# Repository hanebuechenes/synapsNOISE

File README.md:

# synapsNOISE

**synapsNOISE** ist ein analoges Eurorack-Rauschmodul, das eine Vielzahl unterschiedlicher Rauschfarben sowie eine ansteuerbare „Grainy“-Shaper-Sektion bereitstellt. Das Modul wurde entwickelt, um von klassischem weißem Rauschen bis hin zu rauen, texturierten und CV-modulierbaren Rauschstrukturen alles zu liefern.

---

## Funktionen & Signalwege

* **Rauschfarben**: Bereitstellung verschiedener gefilterter Rauschspektren (Weiß, Rot, Pink, Blau, Violett).
* **Grainy-Sektion**: Spezieller Shaper-Zweig mit Dioden-Clipping und CV-Modulation zur Erzeugung von körnigen, raueren Rauschtexturen.
* **Mixer-Stufe**: Integrierter 6-Kanal-Summierer (basierend auf TL072) zum stufenlosen Mischen und Anpassen der Pegel an einem gemeinsamen Ausgang (`Mix Out`).
* **Eingangs- / Generator-Stufen**: Kombiniert Zener-Rauschen, Transistor-Rauschen und logikbasierte Rauschstrukturen (CD4093).

---

## Hardware-Struktur

Das Projekt ist modular im KiCad-Schaltplan aufgeteilt:
* `synapsNOISE.kicad_sch` (Hauptschaltplan)
* `noisesources.kicad_sch` (Rauschquellen)
* `rednoise.kicad_sch`, `pinknoise.kicad_sch`, `bluenoise.kicad_sch`, `violetnoise.kicad_sch` (Filterstufen)
* `grainyout.kicad_sch` (Grainy-Shaper & CV-Sektion)
* `mixer.kicad_sch` (Summierer und Ausgangsstufe)
* `power.kicad_sch` (Stromversorgung & Filterung)

---

## Produktion & Fertigung

Im Ordner `production/` befinden sich alle relevanten Daten für die Leiterplattenfertigung und Bestückung:
* Gerber- und Bohrdateien (`synapsNOISE.zip`)
* Stückliste (`bom.csv` / `bom.ods`)
* Bestückungspositionen (`positions.csv`)

---

## Lizenz & Rechtliches

Dieses Projekt ist Open-Source-Hardware und Open-Source-Software. Die jeweiligen Komponenten unterliegen den folgenden Lizenzen:

| Komponente | Lizenz | Beschreibung |
| :--- | :--- | :--- |
| **Hardware & Platinen** | [CERN OHL v2.0](https://ohwr.org/cernohl) | Gilt für Schaltpläne, PCB-Layouts und CAD-Dateien. |
| **Firmware & Code** | [MIT License](https://opensource.org/licenses/MIT) | Gilt für jeglichen Software- oder Skriptcode im Repository. |

*Entwickelt als Teil der Open-Source Eurorack-Initiative `synaps`. Bei Nachbau, Modifikation oder kommerzieller Nutzung sind die jeweiligen Lizenzbedingungen zu beachten.*

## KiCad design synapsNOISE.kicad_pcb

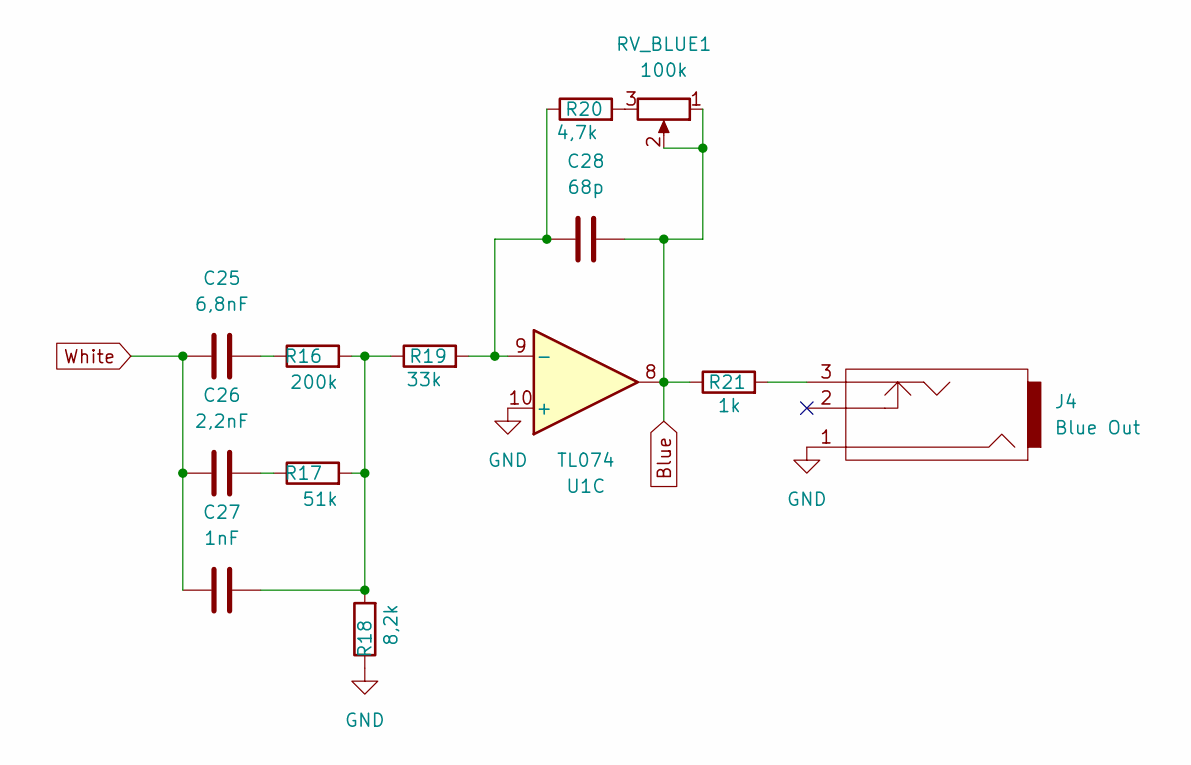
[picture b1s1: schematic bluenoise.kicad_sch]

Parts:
C25: 6,8nF; C_0603_1608Metric_Pad1.08x0.95mm_HandSolder
C26: 2,2nF; C_0603_1608Metric_Pad1.08x0.95mm_HandSolder
C27: 1nF; C_0603_1608Metric_Pad1.08x0.95mm_HandSolder
C28: 68p; C_0603_1608Metric_Pad1.08x0.95mm_HandSolder
J4: Blue Out; PJ301M-12; MFG Part Number WQP-WQP518MA; Digikey Part Number N/A
R16: 200k; R_0603_1608Metric_Pad0.98x0.95mm_HandSolder
R17: 51k; R_0603_1608Metric_Pad0.98x0.95mm_HandSolder
R18: 8,2k; R_0603_1608Metric_Pad0.98x0.95mm_HandSolder
R19: 33k; R_0603_1608Metric_Pad0.98x0.95mm_HandSolder
R20: 4,7k; R_0603_1608Metric_Pad0.98x0.95mm_HandSolder
R21: 1k; R_0603_1608Metric_Pad0.98x0.95mm_HandSolder
RV_BLUE1: 100k; RES-TH_RK09K1130A70
U1: TL074; SOIC-14_3.9x8.7mm_P1.27mm

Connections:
GND: J4.1, R18.1, U1.10 (+); also elsewhere on the board
unnamed: C25.1, R16.1
unnamed: C26.1, R17.1
unnamed: C27.1, R16.2, R17.2, R18.2, R19.1
unnamed: C28.1, R21.1, RV_BLUE1.1, RV_BLUE1.2, U1.8
unnamed: J4.3, R21.2
unnamed: R20.2, RV_BLUE1.3
unnamed: C28.2, R19.2, R20.1, U1.9 (-)
White: C25.2, C26.2, C27.2; also elsewhere on the board

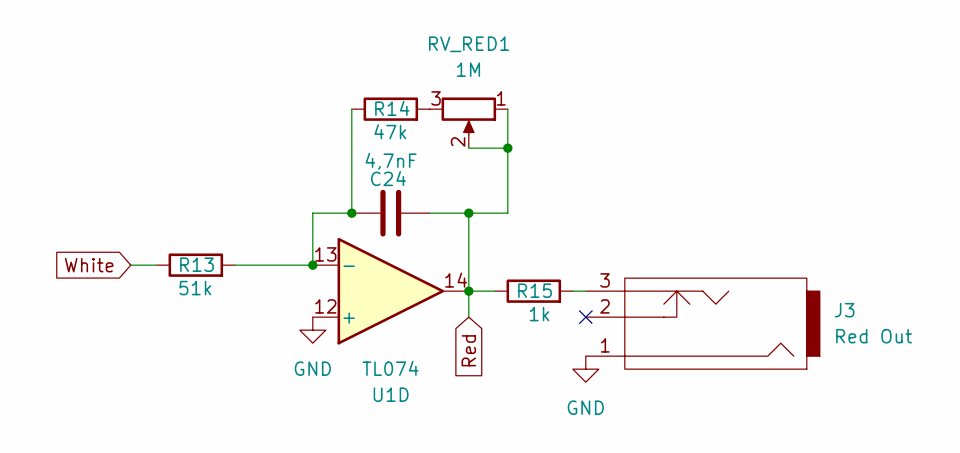
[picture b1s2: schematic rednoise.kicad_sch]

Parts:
C24: 4,7nF; C_0603_1608Metric_Pad1.08x0.95mm_HandSolder
J3: Red Out; PJ301M-12; MFG Part Number WQP-WQP518MA; Digikey Part Number N/A
R13: 51k; R_0603_1608Metric_Pad0.98x0.95mm_HandSolder
R14: 47k; R_0603_1608Metric_Pad0.98x0.95mm_HandSolder
R15: 1k; R_0603_1608Metric_Pad0.98x0.95mm_HandSolder
RV_RED1: 1M; RES-TH_RK09K1130A70
U1: TL074; SOIC-14_3.9x8.7mm_P1.27mm

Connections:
GND: J3.1, U1.12 (+); also elsewhere on the board
unnamed: C24.1, R15.1, RV_RED1.1, RV_RED1.2, U1.14
unnamed: J3.3, R15.2
unnamed: R14.2, RV_RED1.3
unnamed: C24.2, R13.2, R14.1, U1.13 (-)
White: R13.1; also elsewhere on the board

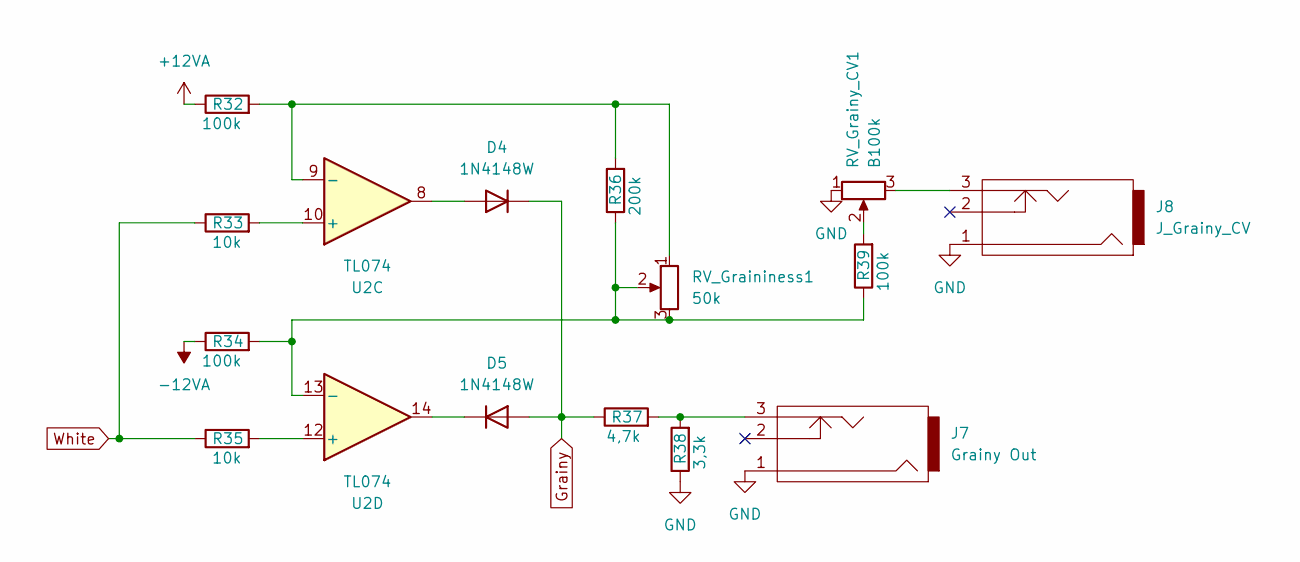
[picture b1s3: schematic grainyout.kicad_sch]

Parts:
D4, D5: 1N4148W; D_SOD-123
J7: Grainy Out; PJ301M-12; MFG Part Number WQP-WQP518MA; Digikey Part Number N/A
J8: J_Grainy_CV; PJ301M-12; MFG Part Number WQP-WQP518MA; Digikey Part Number N/A
R32, R34, R39: 100k; R_0603_1608Metric_Pad0.98x0.95mm_HandSolder
R33, R35: 10k; R_0603_1608Metric_Pad0.98x0.95mm_HandSolder
R36: 200k; R_0603_1608Metric_Pad0.98x0.95mm_HandSolder
R37: 4,7k; R_0603_1608Metric_Pad0.98x0.95mm_HandSolder
R38: 3,3k; R_0603_1608Metric_Pad0.98x0.95mm_HandSolder
RV_Graininess1: 50k; RES-TH_RK09K1130A70
RV_Grainy_CV1: B100k; RES-TH_RK09K1130A70
U2: TL074; SOIC-14_3.9x8.7mm_P1.27mm

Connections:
+12VA: R32.1; also elsewhere on the board
-12VA: R34.1; also elsewhere on the board
GND: J7.1, J8.1, R38.1, RV_Grainy_CV1.1; also elsewhere on the board
unnamed: D4.2 (A), U2.8
unnamed: D4.1 (K), D5.2 (A), R37.1
unnamed: D5.1 (K), U2.14
unnamed: J7.3, R37.2, R38.2
unnamed: J8.3, RV_Grainy_CV1.3
unnamed: R39.2, RV_Grainy_CV1.2
unnamed: R33.2, U2.10 (+)
unnamed: R32.2, R36.2, RV_Graininess1.1, U2.9 (-)
unnamed: R35.2, U2.12 (+)
unnamed: R34.2, R36.1, R39.1, RV_Graininess1.2, RV_Graininess1.3, U2.13 (-)
White: R33.1, R35.1; also elsewhere on the board

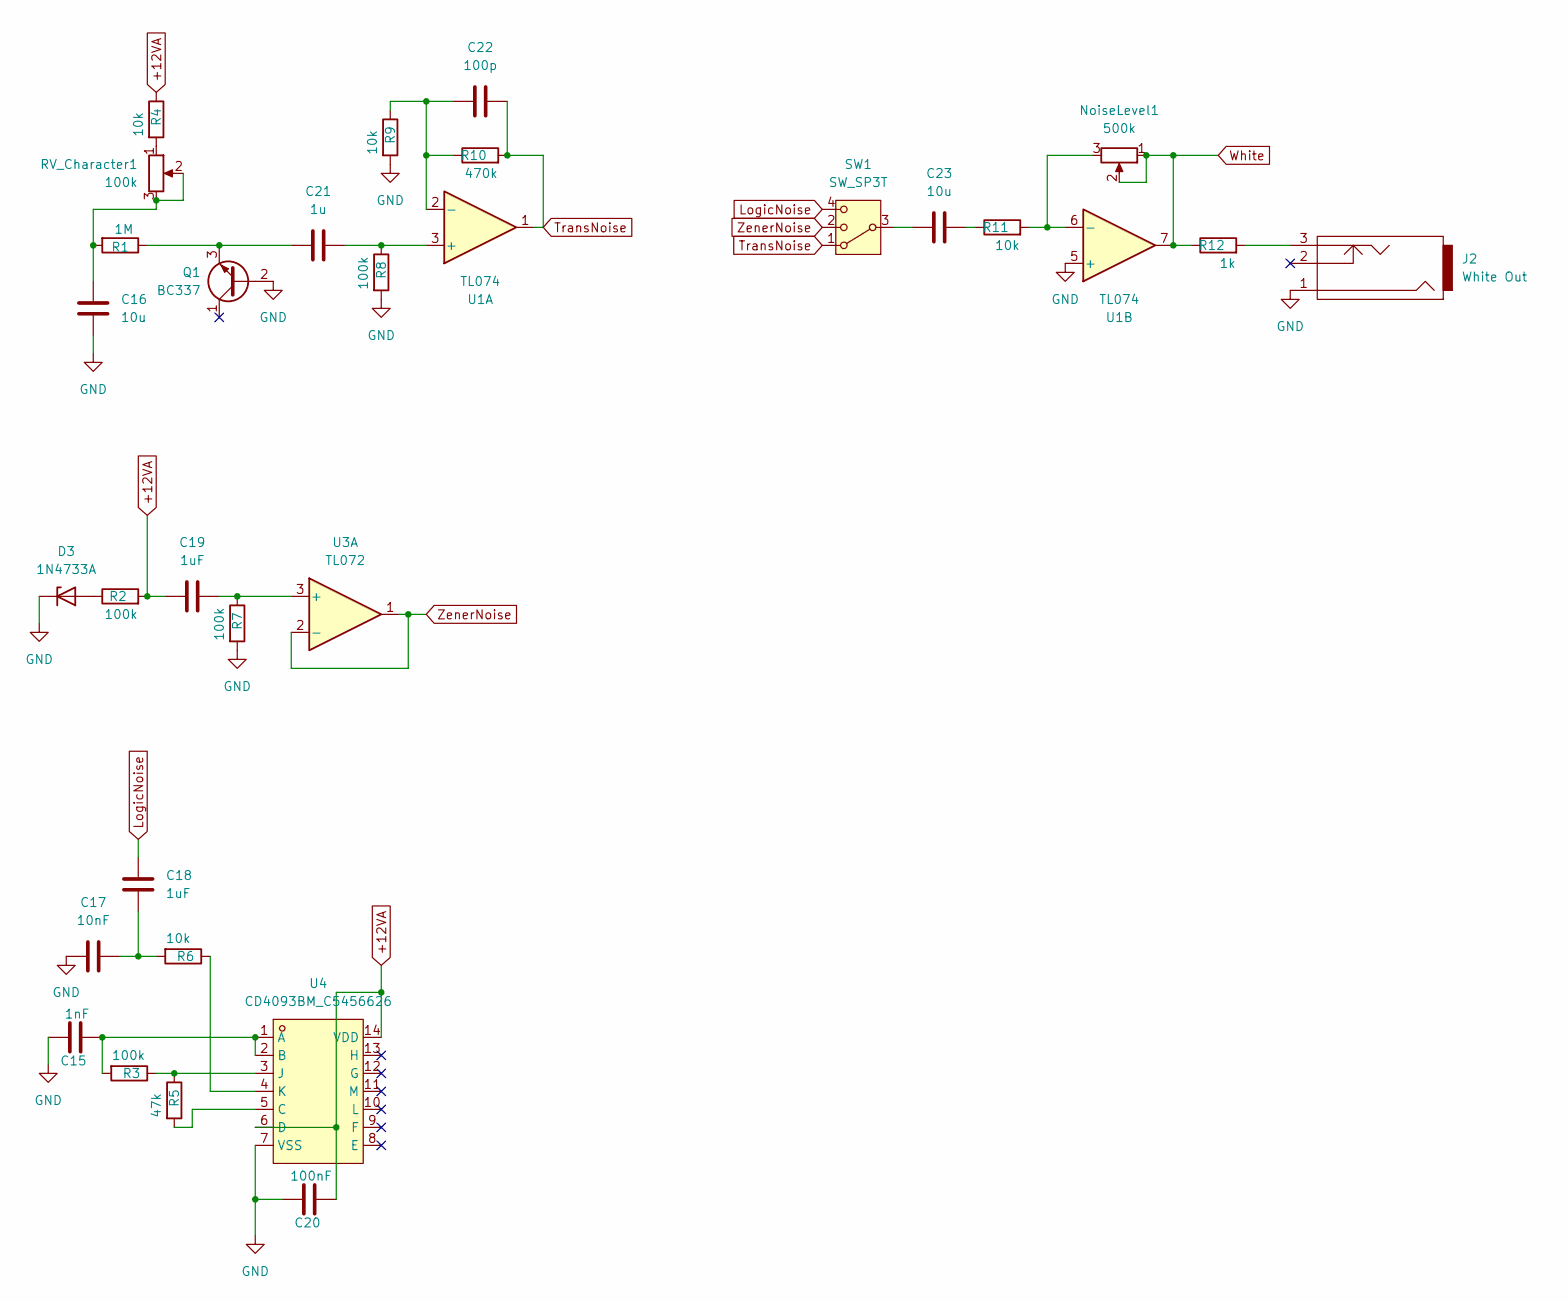
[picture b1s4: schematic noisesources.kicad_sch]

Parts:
C15: 1nF; C_0603_1608Metric_Pad1.08x0.95mm_HandSolder
C16, C23: 10u; C_0603_1608Metric_Pad1.08x0.95mm_HandSolder
C17: 10nF; C_0603_1608Metric_Pad1.08x0.95mm_HandSolder
C18, C19: 1uF; C_0603_1608Metric_Pad1.08x0.95mm_HandSolder
C20: 100nF; C_0603_1608Metric_Pad1.08x0.95mm_HandSolder
C21: 1u; C_0603_1608Metric_Pad1.08x0.95mm_HandSolder
C22: 100p; C_0603_1608Metric_Pad1.08x0.95mm_HandSolder
D3: 1N4733A; D_SOD-123
J2: White Out; PJ301M-12; MFG Part Number WQP-WQP518MA; Digikey Part Number N/A
NoiseLevel1: 500k; RES-TH_RK09K1130A70
Q1: BC337; TO-92_Inline
R1: 1M; R_0603_1608Metric_Pad0.98x0.95mm_HandSolder
R2, R3, R7, R8: 100k; R_0603_1608Metric_Pad0.98x0.95mm_HandSolder
R4, R6, R9, R11: 10k; R_0603_1608Metric_Pad0.98x0.95mm_HandSolder
R5: 47k; R_0603_1608Metric_Pad0.98x0.95mm_HandSolder
R10: 470k; R_0603_1608Metric_Pad0.98x0.95mm_HandSolder
R12: 1k; R_0603_1608Metric_Pad0.98x0.95mm_HandSolder
RV_Character1: 100k; RES-TH_RK09K1130A70
SW1: SW_SP3T; SW_NKK_GW12LJP
U1: TL074; SOIC-14_3.9x8.7mm_P1.27mm
U3: TL072; SOIC-8_3.9x4.9mm_P1.27mm
U4: CD4093BM_C5456626; SOP-14_L8.7-W3.9-P1.27-LS6.0-BL; MPN CD4093BM; LCSC Part C5456626

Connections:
+12VA: C19.2, C20.2, R2.2, R4.1, U4.6 (D), U4.14 (VDD); also elsewhere on the board
GND: C15.1, C16.1, C17.2, C20.1, D3.1 (K), J2.1, Q1.2 (B), R7.2, R8.2, R9.2, U1.5 (+), U4.7 (VSS); also elsewhere on the board
LogicNoise: C18.1, SW1.4
unnamed: C16.2, R1.2, RV_Character1.2, RV_Character1.3
unnamed: C17.1, C18.2, R6.2
unnamed: C23.1, R11.1
unnamed: C23.2, SW1.3
unnamed: D3.2 (A), R2.1
unnamed: J2.3, R12.2
unnamed: C21.2, Q1.3 (E), R1.1
unnamed: R4.2, RV_Character1.1
unnamed: C21.1, R8.1, U1.3 (+)
unnamed: C22.2, R9.1, R10.1, U1.2 (-)
unnamed: NoiseLevel1.3, R11.2, U1.6 (-)
unnamed: C19.1, R7.1, U3.3 (+)
unnamed: C15.2, R3.2, U4.1 (A), U4.2 (B)
unnamed: R5.2, U4.5 (C)
unnamed: R3.1, R5.1, U4.3 (J)
unnamed: R6.1, U4.4 (K)
TransNoise: C22.1, R10.2, SW1.1, U1.1
White: NoiseLevel1.1, NoiseLevel1.2, R12.1, U1.7; also elsewhere on the board
ZenerNoise: SW1.2, U3.1, U3.2 (-)

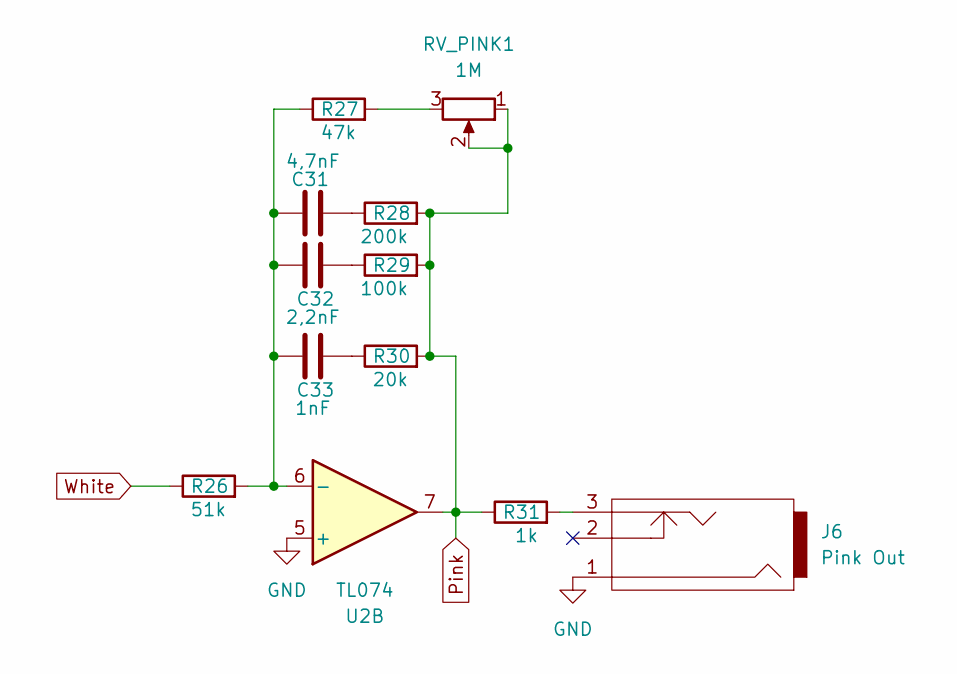
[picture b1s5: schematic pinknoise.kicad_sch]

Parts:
C31: 4,7nF; C_0603_1608Metric_Pad1.08x0.95mm_HandSolder
C32: 2,2nF; C_0603_1608Metric_Pad1.08x0.95mm_HandSolder
C33: 1nF; C_0603_1608Metric_Pad1.08x0.95mm_HandSolder
J6: Pink Out; PJ301M-12; MFG Part Number WQP-WQP518MA; Digikey Part Number N/A
R26: 51k; R_0603_1608Metric_Pad0.98x0.95mm_HandSolder
R27: 47k; R_0603_1608Metric_Pad0.98x0.95mm_HandSolder
R28: 200k; R_0603_1608Metric_Pad0.98x0.95mm_HandSolder
R29: 100k; R_0603_1608Metric_Pad0.98x0.95mm_HandSolder
R30: 20k; R_0603_1608Metric_Pad0.98x0.95mm_HandSolder
R31: 1k; R_0603_1608Metric_Pad0.98x0.95mm_HandSolder
RV_PINK1: 1M; RES-TH_RK09K1130A70
U2: TL074; SOIC-14_3.9x8.7mm_P1.27mm

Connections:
GND: J6.1, U2.5 (+); also elsewhere on the board
unnamed: C31.1, R28.1
unnamed: C32.2, R29.1
unnamed: C33.2, R30.1
unnamed: J6.3, R31.2
unnamed: R27.2, RV_PINK1.3
unnamed: R28.2, R29.2, R30.2, R31.1, RV_PINK1.1, RV_PINK1.2, U2.7
unnamed: C31.2, C32.1, C33.1, R26.2, R27.1, U2.6 (-)
White: R26.1; also elsewhere on the board

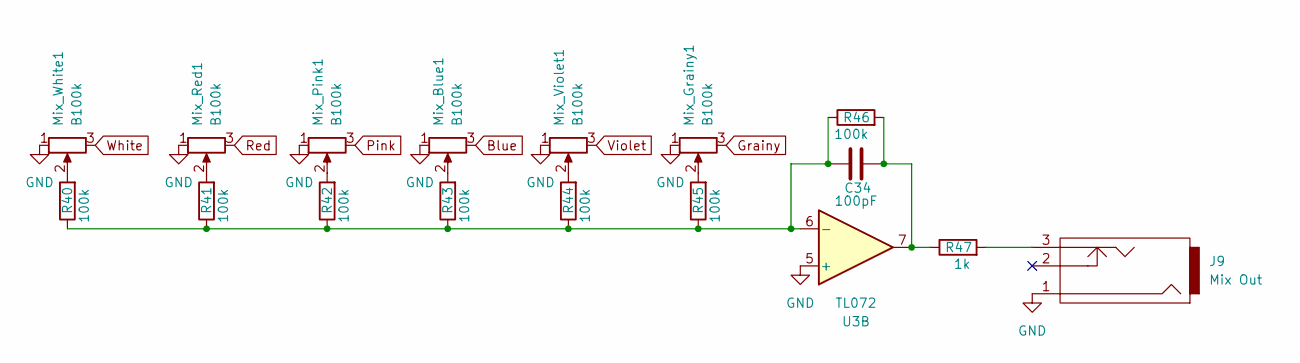
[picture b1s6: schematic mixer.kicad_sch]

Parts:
C34: 100pF; C_0603_1608Metric_Pad1.08x0.95mm_HandSolder
J9: Mix Out; PJ301M-12; MFG Part Number WQP-WQP518MA; Digikey Part Number N/A
Mix_Blue1: B100k; RES-TH_RK09K1130A70
Mix_Grainy1: B100k; RES-TH_RK09K1130A70
Mix_Pink1: B100k; RES-TH_RK09K1130A70
Mix_Red1: B100k; RES-TH_RK09K1130A70
Mix_Violet1: B100k; RES-TH_RK09K1130A70
Mix_White1: B100k; RES-TH_RK09K1130A70
R40, R41, R42, R43, R44, R45, R46: 100k; R_0603_1608Metric_Pad0.98x0.95mm_HandSolder
R47: 1k; R_0603_1608Metric_Pad0.98x0.95mm_HandSolder
U3: TL072; SOIC-8_3.9x4.9mm_P1.27mm

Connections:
Blue: Mix_Blue1.3
GND: J9.1, Mix_Blue1.1, Mix_Grainy1.1, Mix_Pink1.1, Mix_Red1.1, Mix_Violet1.1, Mix_White1.1, U3.5 (+); also elsewhere on the board
Grainy: Mix_Grainy1.3
unnamed: C34.2, R46.2, R47.1, U3.7
unnamed: J9.3, R47.2
unnamed: Mix_Blue1.2, R43.2
unnamed: Mix_Grainy1.2, R45.2
unnamed: Mix_Pink1.2, R42.2
unnamed: Mix_Red1.2, R41.2
unnamed: Mix_Violet1.2, R44.2
unnamed: Mix_White1.2, R40.2
unnamed: C34.1, R40.1, R41.1, R42.1, R43.1, R44.1, R45.1, R46.1, U3.6 (-)
Pink: Mix_Pink1.3
Red: Mix_Red1.3
Violet: Mix_Violet1.3
White: Mix_White1.3; also elsewhere on the board

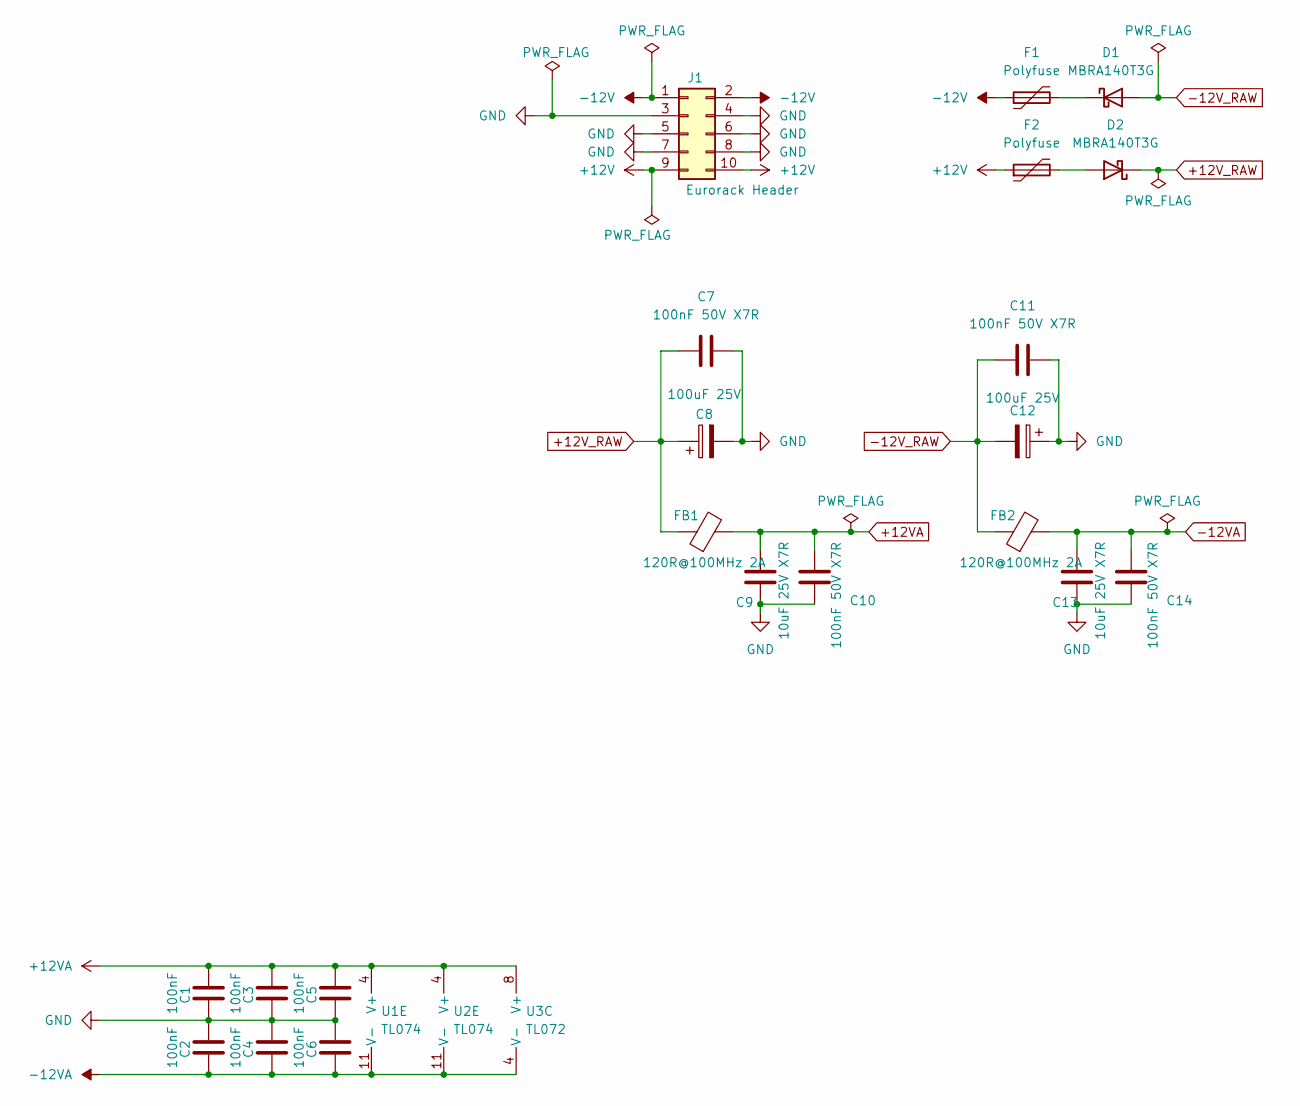
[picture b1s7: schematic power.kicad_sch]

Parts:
C1, C2, C3, C4, C5, C6: 100nF; C_0603_1608Metric_Pad1.08x0.95mm_HandSolder
C7, C10, C11, C14: 100nF 50V X7R; C_0603_1608Metric_Pad1.08x0.95mm_HandSolder
C8, C12: 100uF 25V; CP_Elec_6.3x7.7
C9, C13: 10uF 25V X7R; C_0805_2012Metric_Pad1.18x1.45mm_HandSolder
D1, D2: MBRA140T3G; D_SMA-SMB_Universal_Handsoldering
F1, F2: Polyfuse; Fuse_1210_3225Metric
FB1, FB2: 120R@100MHz 2A; L_0603_1608Metric_Pad1.05x0.95mm_HandSolder
J1: Eurorack Header; PinHeader_2x05_P2.54mm_Vertical
U1, U2: TL074; SOIC-14_3.9x8.7mm_P1.27mm
U3: TL072; SOIC-8_3.9x4.9mm_P1.27mm

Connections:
+12V: F2.1, J1.9, J1.10
+12VA: C1.1, C3.1, C5.1, C9.1, C10.1, FB1.2, U1.4 (V+), U2.4 (V+), U3.8 (V+); also elsewhere on the board
+12V_RAW: C7.1, C8.1, D2.1 (K), FB1.1
-12V: F1.1, J1.1, J1.2
-12VA: C2.2, C4.2, C6.2, C13.1, C14.1, FB2.2, U1.11 (V-), U2.11 (V-), U3.4 (V-); also elsewhere on the board
-12V_RAW: C11.1, C12.2, D1.2 (A), FB2.1
GND: C1.2, C2.1, C3.2, C4.1, C5.2, C6.1, C7.2, C8.2, C9.2, C10.2, C11.2, C12.1, C13.2, C14.2, J1.3, J1.4, J1.5, J1.6, J1.7, J1.8; also elsewhere on the board
unnamed: D1.1 (K), F1.2
unnamed: D2.2 (A), F2.2

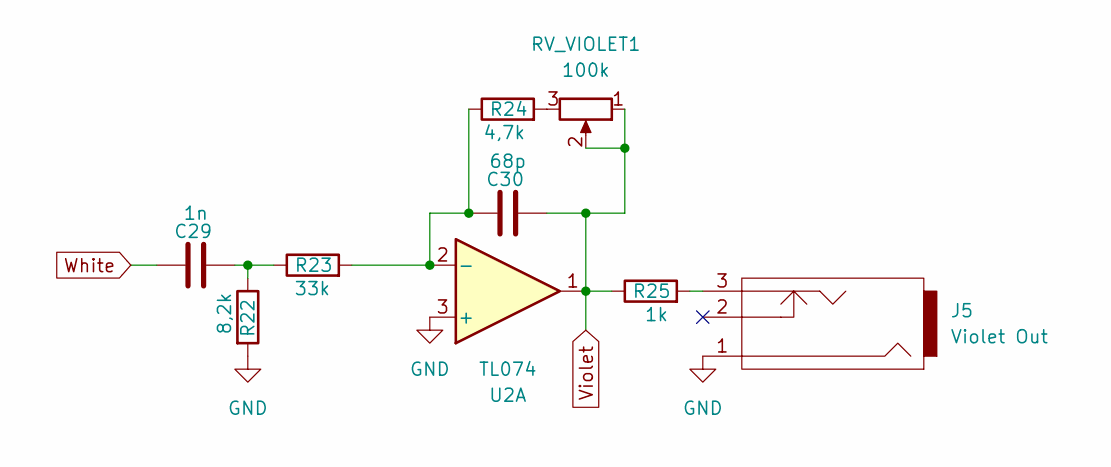
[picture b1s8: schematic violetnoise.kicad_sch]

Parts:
C29: 1n; C_0603_1608Metric_Pad1.08x0.95mm_HandSolder
C30: 68p; C_0603_1608Metric_Pad1.08x0.95mm_HandSolder
J5: Violet Out; PJ301M-12; MFG Part Number WQP-WQP518MA; Digikey Part Number N/A
R22: 8,2k; R_0603_1608Metric_Pad0.98x0.95mm_HandSolder
R23: 33k; R_0603_1608Metric_Pad0.98x0.95mm_HandSolder
R24: 4,7k; R_0603_1608Metric_Pad0.98x0.95mm_HandSolder
R25: 1k; R_0603_1608Metric_Pad0.98x0.95mm_HandSolder
RV_VIOLET1: 100k; RES-TH_RK09K1130A70
U2: TL074; SOIC-14_3.9x8.7mm_P1.27mm

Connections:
GND: J5.1, R22.2, U2.3 (+); also elsewhere on the board
unnamed: C29.1, R22.1, R23.1
unnamed: C30.1, R25.1, RV_VIOLET1.1, RV_VIOLET1.2, U2.1
unnamed: J5.3, R25.2
unnamed: R24.2, RV_VIOLET1.3
unnamed: C30.2, R23.2, R24.1, U2.2 (-)
White: C29.2; also elsewhere on the board

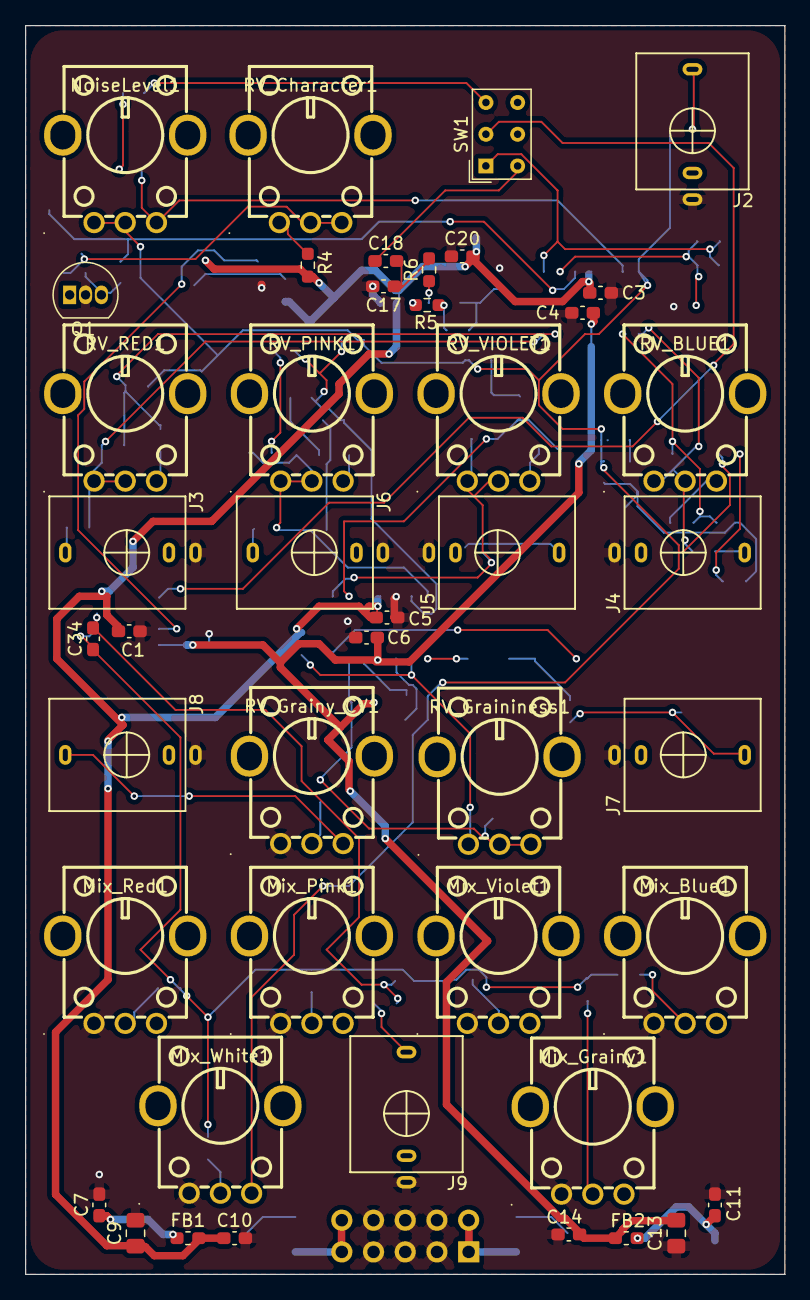
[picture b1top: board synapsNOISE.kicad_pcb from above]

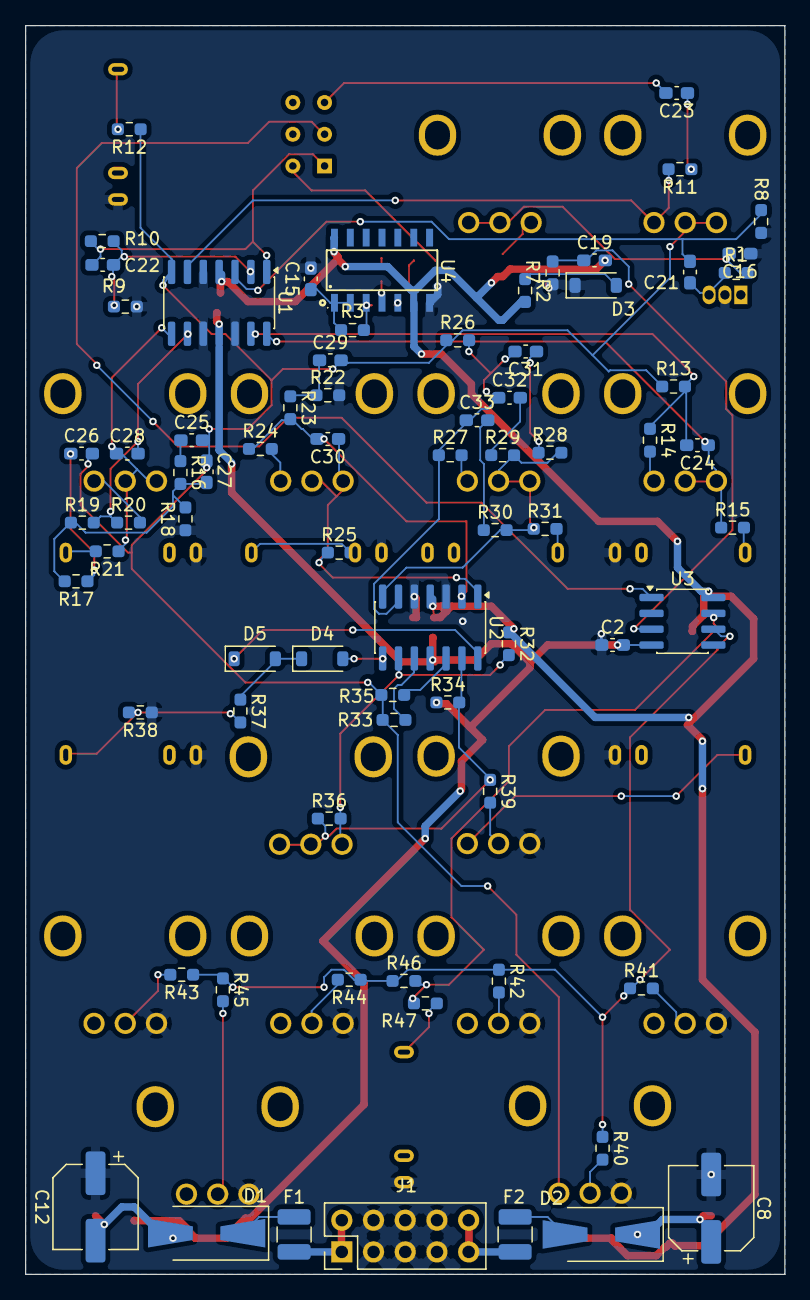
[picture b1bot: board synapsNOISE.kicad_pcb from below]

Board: 2 copper layers, 60.8 x 100.0 mm, 119 parts (75 on the bottom side), 71 nets.

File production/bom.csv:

Designator,Footprint,Quantity,Value,LCSC Part #
"C1, C2, C20, C3, C4, C5, C6",0603,7,100nF,
"C10, C11, C14, C7",0603,4,100nF 50V X7R,
"C12, C8",CP_Elec_6.3x7.7,2,100uF 25V,
"C13, C9",0805,2,10uF 25V X7R,
"C15, C27, C33",0603,3,1nF,
"C16, C23",0603,2,10u,
C17,0603,1,10nF,
"C18, C19",0603,2,1uF,
C21,0603,1,1u,
C22,0603,1,100p,
"C24, C31",0603,2,"4,7nF",
C25,0603,1,"6,8nF",
"C26, C32",0603,2,"2,2nF",
"C28, C30",0603,2,68p,
C29,0603,1,1n,
C34,0603,1,100pF,
"D1, D2",D_SMA-SMB_Universal_Handsoldering,2,MBRA140T3G,
D3,D_SOD-123,1,1N4733A,
"D4, D5",D_SOD-123,2,1N4148W,
"F1, F2",1210,2,Polyfuse,
"FB1, FB2",0603,2,120R@100MHz 2A,
J1,PinHeader_2x05_P2.54mm_Vertical,1,Eurorack Header,
J2,PJ301M-12,1,White Out,
J3,PJ301M-12,1,Red Out,
J4,PJ301M-12,1,Blue Out,
J5,PJ301M-12,1,Violet Out,
J6,PJ301M-12,1,Pink Out,
J7,PJ301M-12,1,Grainy Out,
J8,PJ301M-12,1,J_Grainy_CV,
J9,PJ301M-12,1,Mix Out,
"MIX_BLUE1, MIX_GRAINY1, MIX_PINK1, MIX_RED1, MIX_VIOLET1, MIX_WHITE1, RV_GRAINY_CV1",RES-TH_RK09K1130A70,7,B100k,
NOISELEVEL1,RES-TH_RK09K1130A70,1,500k,
Q1,TO-92_Inline,1,BC337,
R1,0603,1,1M,
R10,0603,1,470k,
"R11, R33, R35, R4, R6, R9",0603,6,10k,
"R12, R15, R21, R25, R31, R47",0603,6,1k,
"R13, R17, R26",0603,3,51k,
"R14, R27, R5",0603,3,47k,
"R16, R28, R36",0603,3,200k,
"R18, R22",0603,2,"8,2k",
"R19, R23",0603,2,33k,
"R2, R29, R3, R32, R34, R39, R40, R41, R42, R43, R44, R45, R46, R7, R8",0603,15,100k,
"R20, R24, R37",0603,3,"4,7k",
R30,0603,1,20k,
R38,0603,1,"3,3k",
"RV_BLUE1, RV_CHARACTER1, RV_VIOLET1",RES-TH_RK09K1130A70,3,100k,
RV_GRAININESS1,RES-TH_RK09K1130A70,1,50k,
"RV_PINK1, RV_RED1",RES-TH_RK09K1130A70,2,1M,
SW1,SW_NKK_GW12LJP,1,SW_SP3T,
"U1, U2",SOIC-14_3.9x8.7mm_P1.27mm,2,TL074,
U3,SOIC-8_3.9x4.9mm_P1.27mm,1,TL072,
U4,SOP-14_L8.7-W3.9-P1.27-LS6.0-BL,1,CD4093BM_C5456626,C5456626
